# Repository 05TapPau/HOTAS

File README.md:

Hi, im a student in a technological highschool and this is a project I did.
in this repo you should be able to find all things and sources to somewhat clone my project
well its not gonna be a copy and paste project for anyone trying cuz you have to figure our some stuff on your own or you ask me rreddit: https://www.reddit.com/user/gimme_da_meme/

maybe i will add some links in here sometime but right ow its 23:28 where im at and i wanna go to sleep so yeah sorry for that i guess

anyways have a great night/morning/day

Copyright (C) 2025 "Paul Tappeiner" aka "05TapPau"
These Sources are freely available: 
You may distribute and/or modify them under the terms of the GNU General Public License, either 
according to version 3 of the license or any later version, as published by the Free Software Foundation.
These Sources are distributed in the hope that they will be useful, but WITHOUT ANY WARRANTY; even without 
the implied warranty of MERCHANTABILITY or FITNESS FOR A PARTICULAR PURPOSE. 
For further details, see the GNU General Public License.

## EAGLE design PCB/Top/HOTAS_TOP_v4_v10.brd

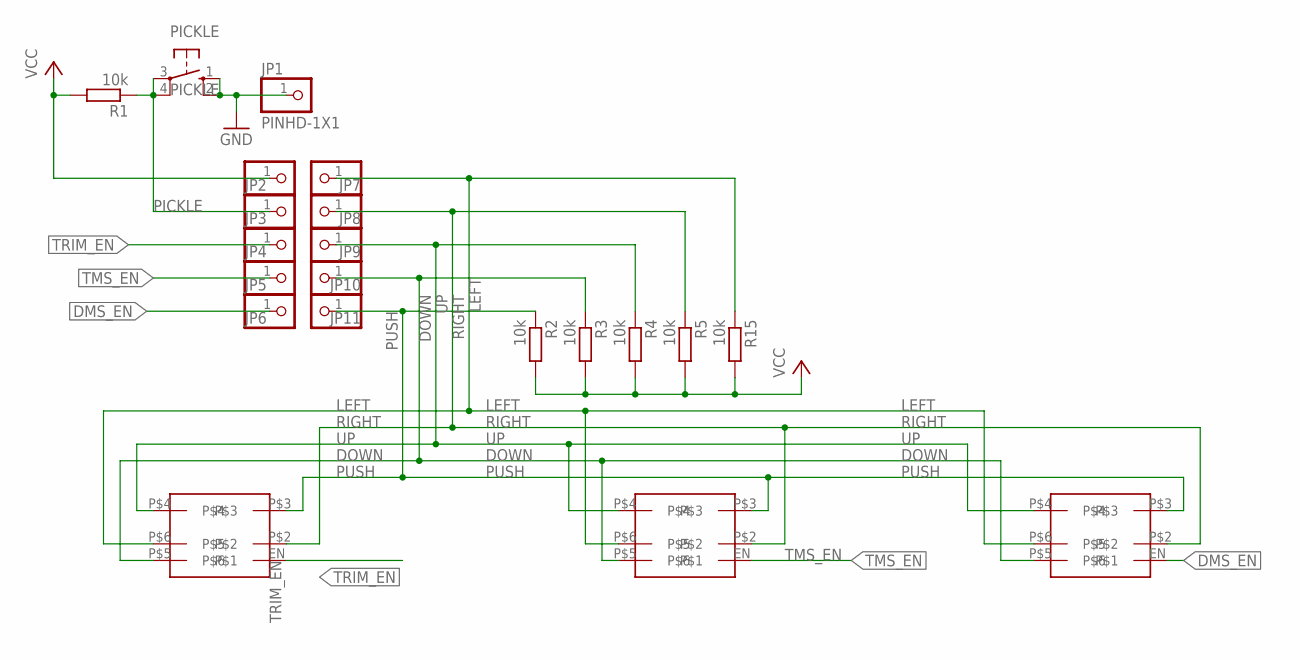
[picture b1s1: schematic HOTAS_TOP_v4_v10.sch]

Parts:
JP1, JP2, JP3, JP4, JP5, JP6, JP7, JP8, JP9, JP10, JP11: PINHD-1X1; 1X01
PICKLE: 10-XX; B3F-10XX
R1, R2, R3, R4, R5, R15: 10k; RESC3216X70
U$1, U$2, U$3: FIVEWAYHATSSMD

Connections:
DMS_EN: JP6.1, U$3.EN
DOWN: JP10.1, R3.1, U$1.P$5, U$2.P$5, U$3.P$5
GND: JP1.1, PICKLE.1 (S), PICKLE.2 (S1)
LEFT: JP7.1, R15.1, U$1.P$6, U$2.P$6, U$3.P$6
PICKLE: JP3.1, PICKLE.3, PICKLE.4 (P1), R1.1
PUSH: JP11.1, R2.1, U$1.P$3, U$2.P$3, U$3.P$3
RIGHT: JP8.1, R5.1, U$1.P$2, U$2.P$2, U$3.P$2
TMS_EN: JP5.1, U$2.EN
TRIM_EN: JP4.1, U$1.EN
UP: JP9.1, R4.1, U$1.P$4, U$2.P$4, U$3.P$4
VCC: JP2.1, R1.2, R2.2, R3.2, R4.2, R5.2, R15.2

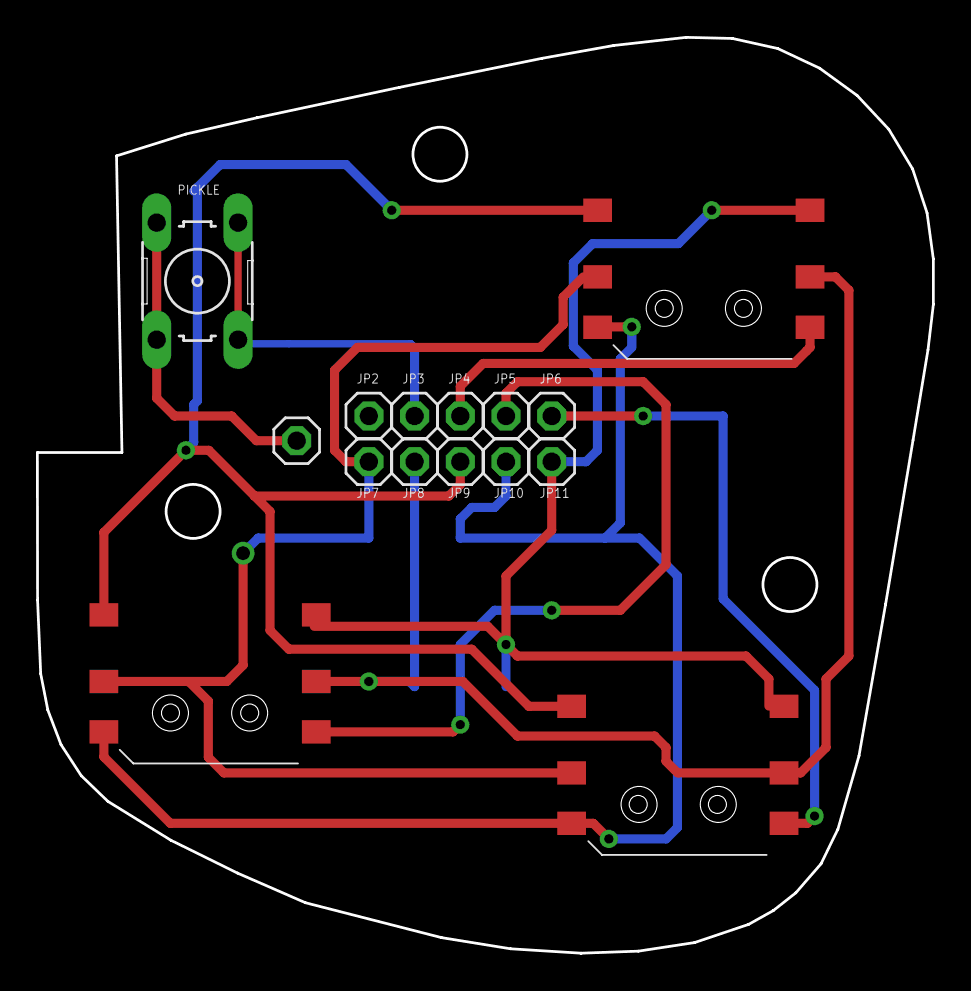
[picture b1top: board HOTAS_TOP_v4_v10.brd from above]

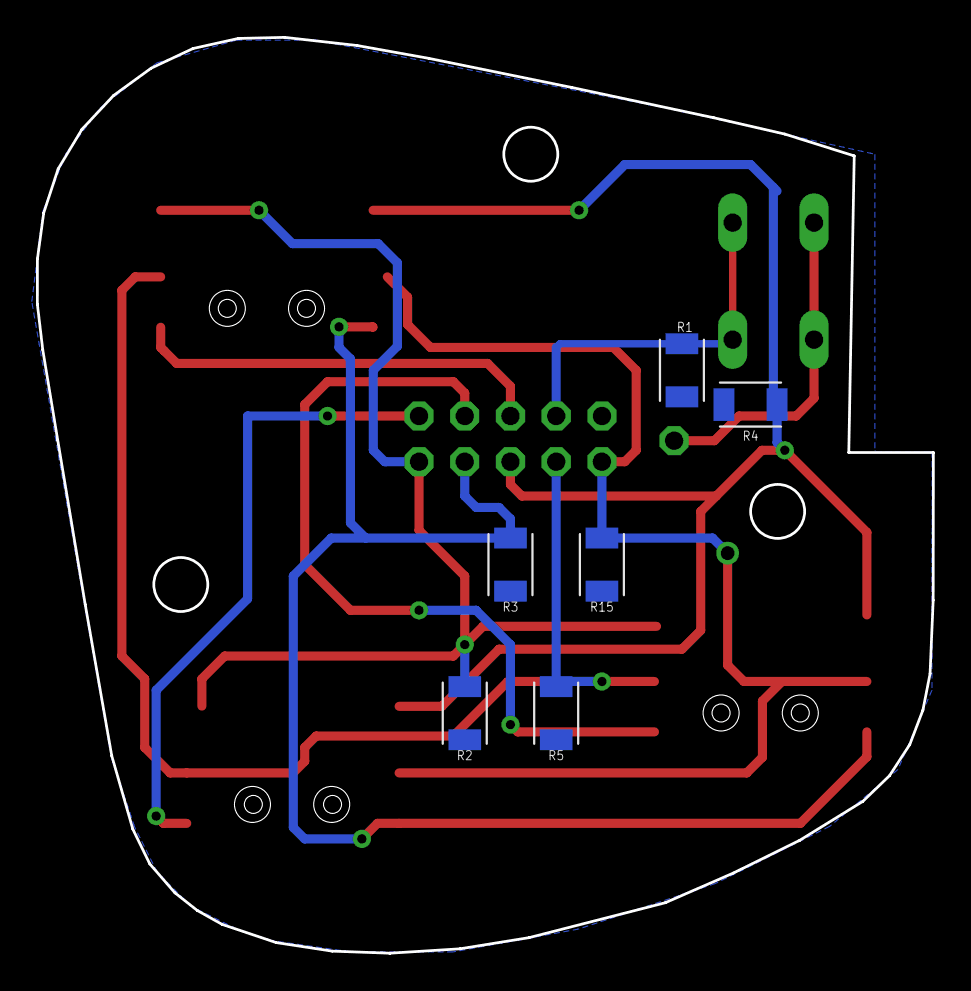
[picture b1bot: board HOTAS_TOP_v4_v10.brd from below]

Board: 2 copper layers, 49.8 x 50.9 mm, 21 parts (6 on the bottom side), 11 nets.

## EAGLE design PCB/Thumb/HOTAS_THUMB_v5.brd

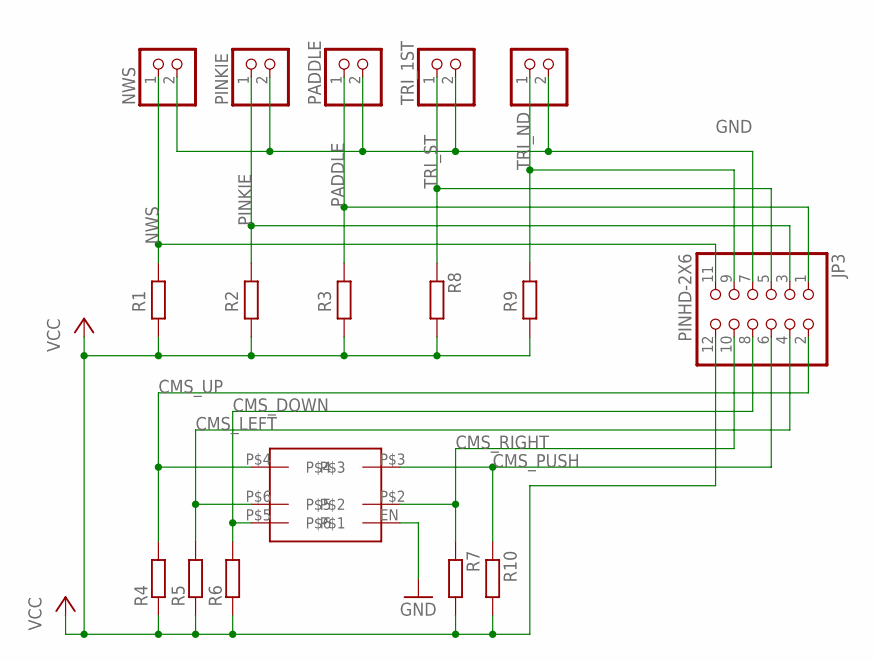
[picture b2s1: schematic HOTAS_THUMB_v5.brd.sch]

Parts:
JP3: PINHD-2X6; 2X06
NWS: PINHD-1X2; 1X02
PADDLE: PINHD-1X2; 1X02
PINKIE: PINHD-1X2; 1X02
R1, R2, R3, R4, R5, R6, R7, R8, R9, R10: R_CHIP-1206(3216-METRIC); RESC3216X70
TRI_1ST: PINHD-1X2; 1X02
TRI_ND: PINHD-1X2; 1X02
U$1: FIVEWAYHATSSMD

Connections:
CMS_DOWN: JP3.8, R6.2, U$1.P$5
CMS_LEFT: JP3.4, R5.2, U$1.P$6
CMS_PUSH: JP3.6, R10.1, U$1.P$3
CMS_RIGHT: JP3.10, R7.1, U$1.P$2
CMS_UP: JP3.2, R4.2, U$1.P$4
GND: JP3.7, NWS.2, PADDLE.2, PINKIE.2, TRI_1ST.2, TRI_ND.2, U$1.EN
NWS: JP3.11, NWS.1, R1.1
PADDLE: JP3.1, PADDLE.1, R3.1
PINKIE: JP3.3, PINKIE.1, R2.1
TRI_ND: JP3.9, R9.1, TRI_ND.1
TRI_ST: JP3.5, R8.1, TRI_1ST.1
VCC: JP3.12, R1.2, R2.2, R3.2, R4.1, R5.1, R6.1, R7.2, R8.2, R9.2, R10.2

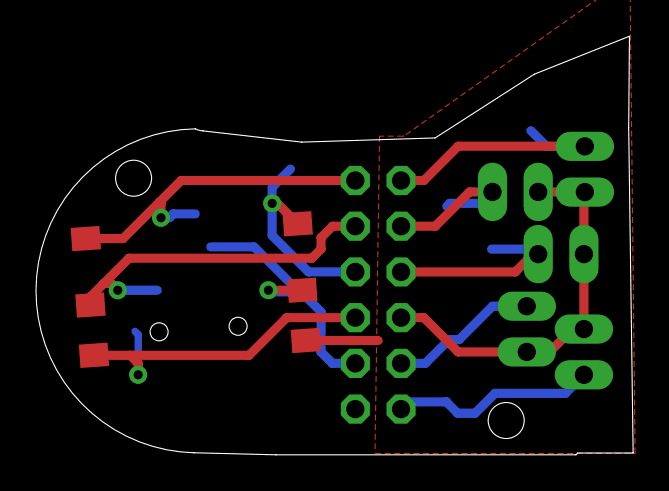
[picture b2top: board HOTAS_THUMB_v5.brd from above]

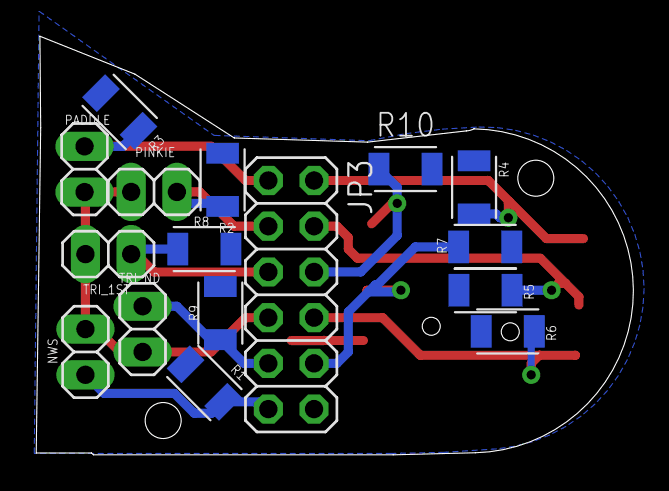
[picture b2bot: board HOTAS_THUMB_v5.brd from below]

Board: 2 copper layers, 33.2 x 23.3 mm, 17 parts (16 on the bottom side), 12 nets.

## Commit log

2024-05-22 ready?
2024-08-14 added stuff
    added:
    - code from old repo
    - documentation only german for now
2024-08-14 english documentation
2025-08-14 pptx
2025-08-14 fixed
